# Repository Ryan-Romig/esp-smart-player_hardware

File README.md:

#Board layout and schematics for embedded device. 
KiCad project - work in progress

MCU - esp32-s2 -- chose s2 because of built in USB controller to allow mass storage mode (uploading mp3 via usb)

ram - TBD
power supply - TBD

dac-MCP4725 -- small 12 bit 12c -- needs amplifier
amplifier -- LM386

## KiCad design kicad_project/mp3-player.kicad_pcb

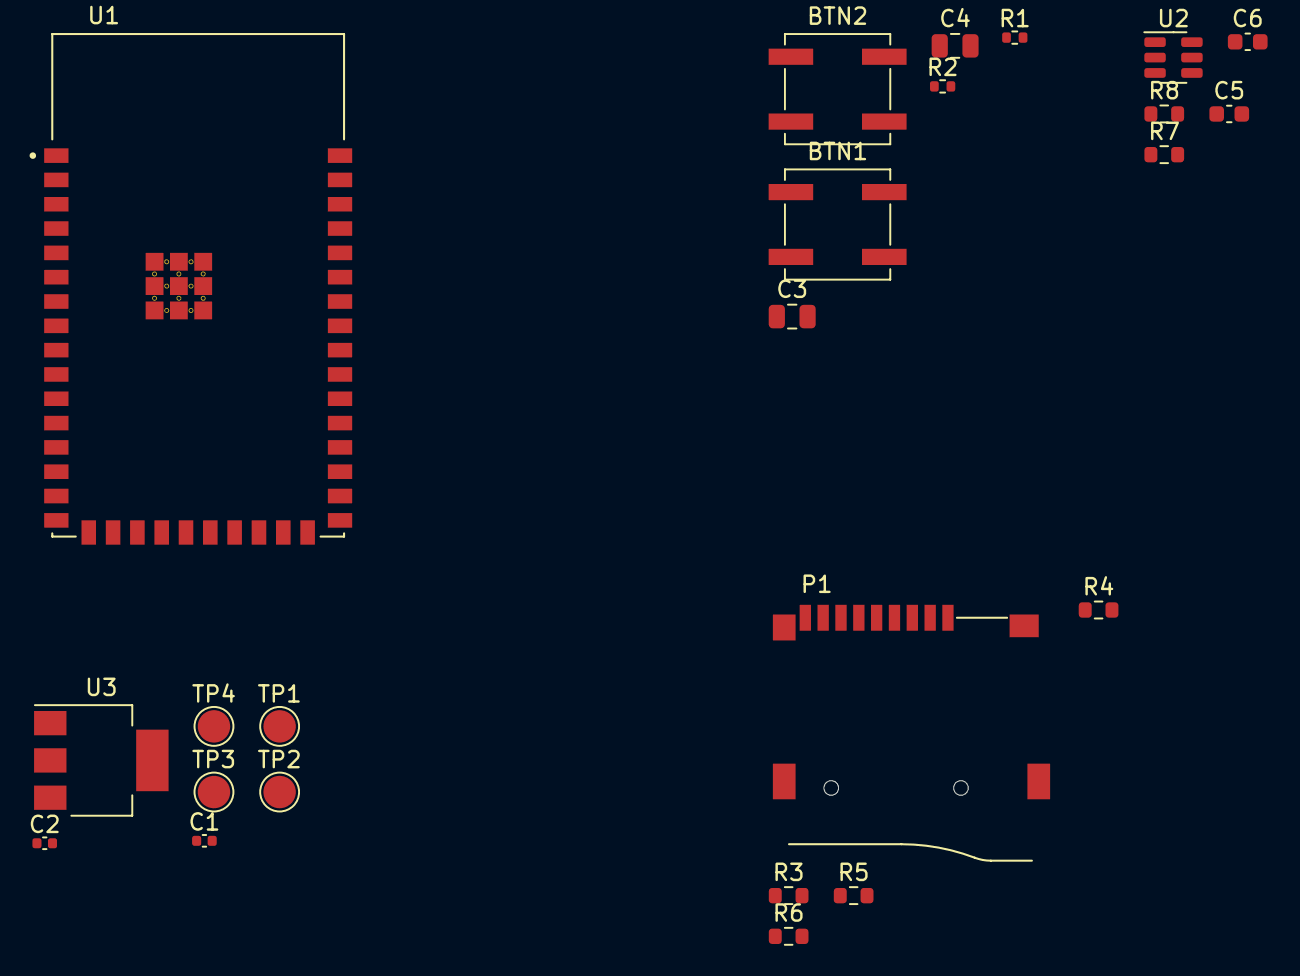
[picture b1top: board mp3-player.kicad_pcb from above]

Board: 2 copper layers, 24 parts (0 on the bottom side), 14 nets, no tracks yet.

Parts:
BTN1, BTN2: SPST-SMD-5.2MM; SW_SPST_B3SL-1022P
C1, C2: 100nF; C_0402_1005Metric
C3, C4: 1uF; C_0805_2012Metric
C5: 10uf; C_0603_1608Metric
C6: 0.1uf; C_0603_1608Metric
P1: ST-TF-003A; SUNTECH_ST-TF-003A
R1: R?; R_0402_1005Metric
R2: R-EU_R0603; R_0402_1005Metric
R3, R4, R5, R6: R-EU_R0603; R_0603_1608Metric
R7, R8: 10k; R_0603_1608Metric
TP1: 5V_USB; TestPoint_Pad_D2.0mm
TP2: USB_D-; TestPoint_Pad_D2.0mm
TP3: USB_D+; TestPoint_Pad_D2.0mm
TP4: USB_GND; TestPoint_Pad_D2.0mm
U1: ESP32-S2-WROVER; MODULE_ESP32-S2-WROVER
U2: MCP4725xxx-xCH; SOT-23-6
U3: LM1117; SOT-223

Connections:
DAC_SCL: R7.1, U1.28 (IO34), U2.5 (SCL)
DAC_SDA: R8.2, U1.29 (IO35), U2.4 (SDA)
EN: BTN2.2, C4.1, R2.2, U1.41 (EN)
GND: BTN1.1, BTN2.1, C1.2, C2.2, C3.1, C4.2, P1.6 (VSS), P1.G1 (GND), P1.G2 (GND), P1.G3 (GND), P1.G4 (GND), TP4.1, U1.1 (GND), U1.26 (GND), U1.42 (GND), U2.2 (VSS), U2.6 (A0), U3.1 (GND)
IO0: BTN1.2, C3.2, R1.2, U1.3 (IO0)
unnamed: U1.43_1 (EXP), U1.43_2 (EXP), U1.43_3 (EXP), U1.43_4 (EXP), U1.43_5 (EXP), U1.43_6 (EXP), U1.43_7 (EXP), U1.43_8 (EXP), U1.43_9 (EXP), U1.43_10 (EXP), U1.43_11 (EXP), U1.43_12 (EXP), U1.43_13 (EXP), U1.43_14 (EXP), U1.43_15 (EXP), U1.43_16 (EXP), U1.43_17 (EXP), U1.43_18 (EXP), U1.43_19 (EXP), U1.43_20 (EXP), U1.43_21 (EXP)
SD_CLK: P1.5 (CLK), R6.2, U1.17 (IO14)
SD_CMD: P1.3 (CMD), R5.2, U1.18 (IO15)
SD_D0: P1.7 (DAT0), R4.1, U1.5 (IO2)
SD_D3: P1.2 (DAT3), R3.1, U1.16 (IO13)
USB_D+: TP3.1, U1.23 (IO20)
USB_D-: TP2.1, U1.22 (IO19)
VDD: C1.1, C5.1, C6.1, P1.4 (VDD), R1.1, R2.1, R3.2, R4.2, R5.1, R6.1, R7.2, R8.1, U1.2 (3V3), U2.3 (VDD), U3.2 (UOUT)
VUSB: C2.1, TP1.1, U3.3 (VIN)

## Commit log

2022-12-18 initial
